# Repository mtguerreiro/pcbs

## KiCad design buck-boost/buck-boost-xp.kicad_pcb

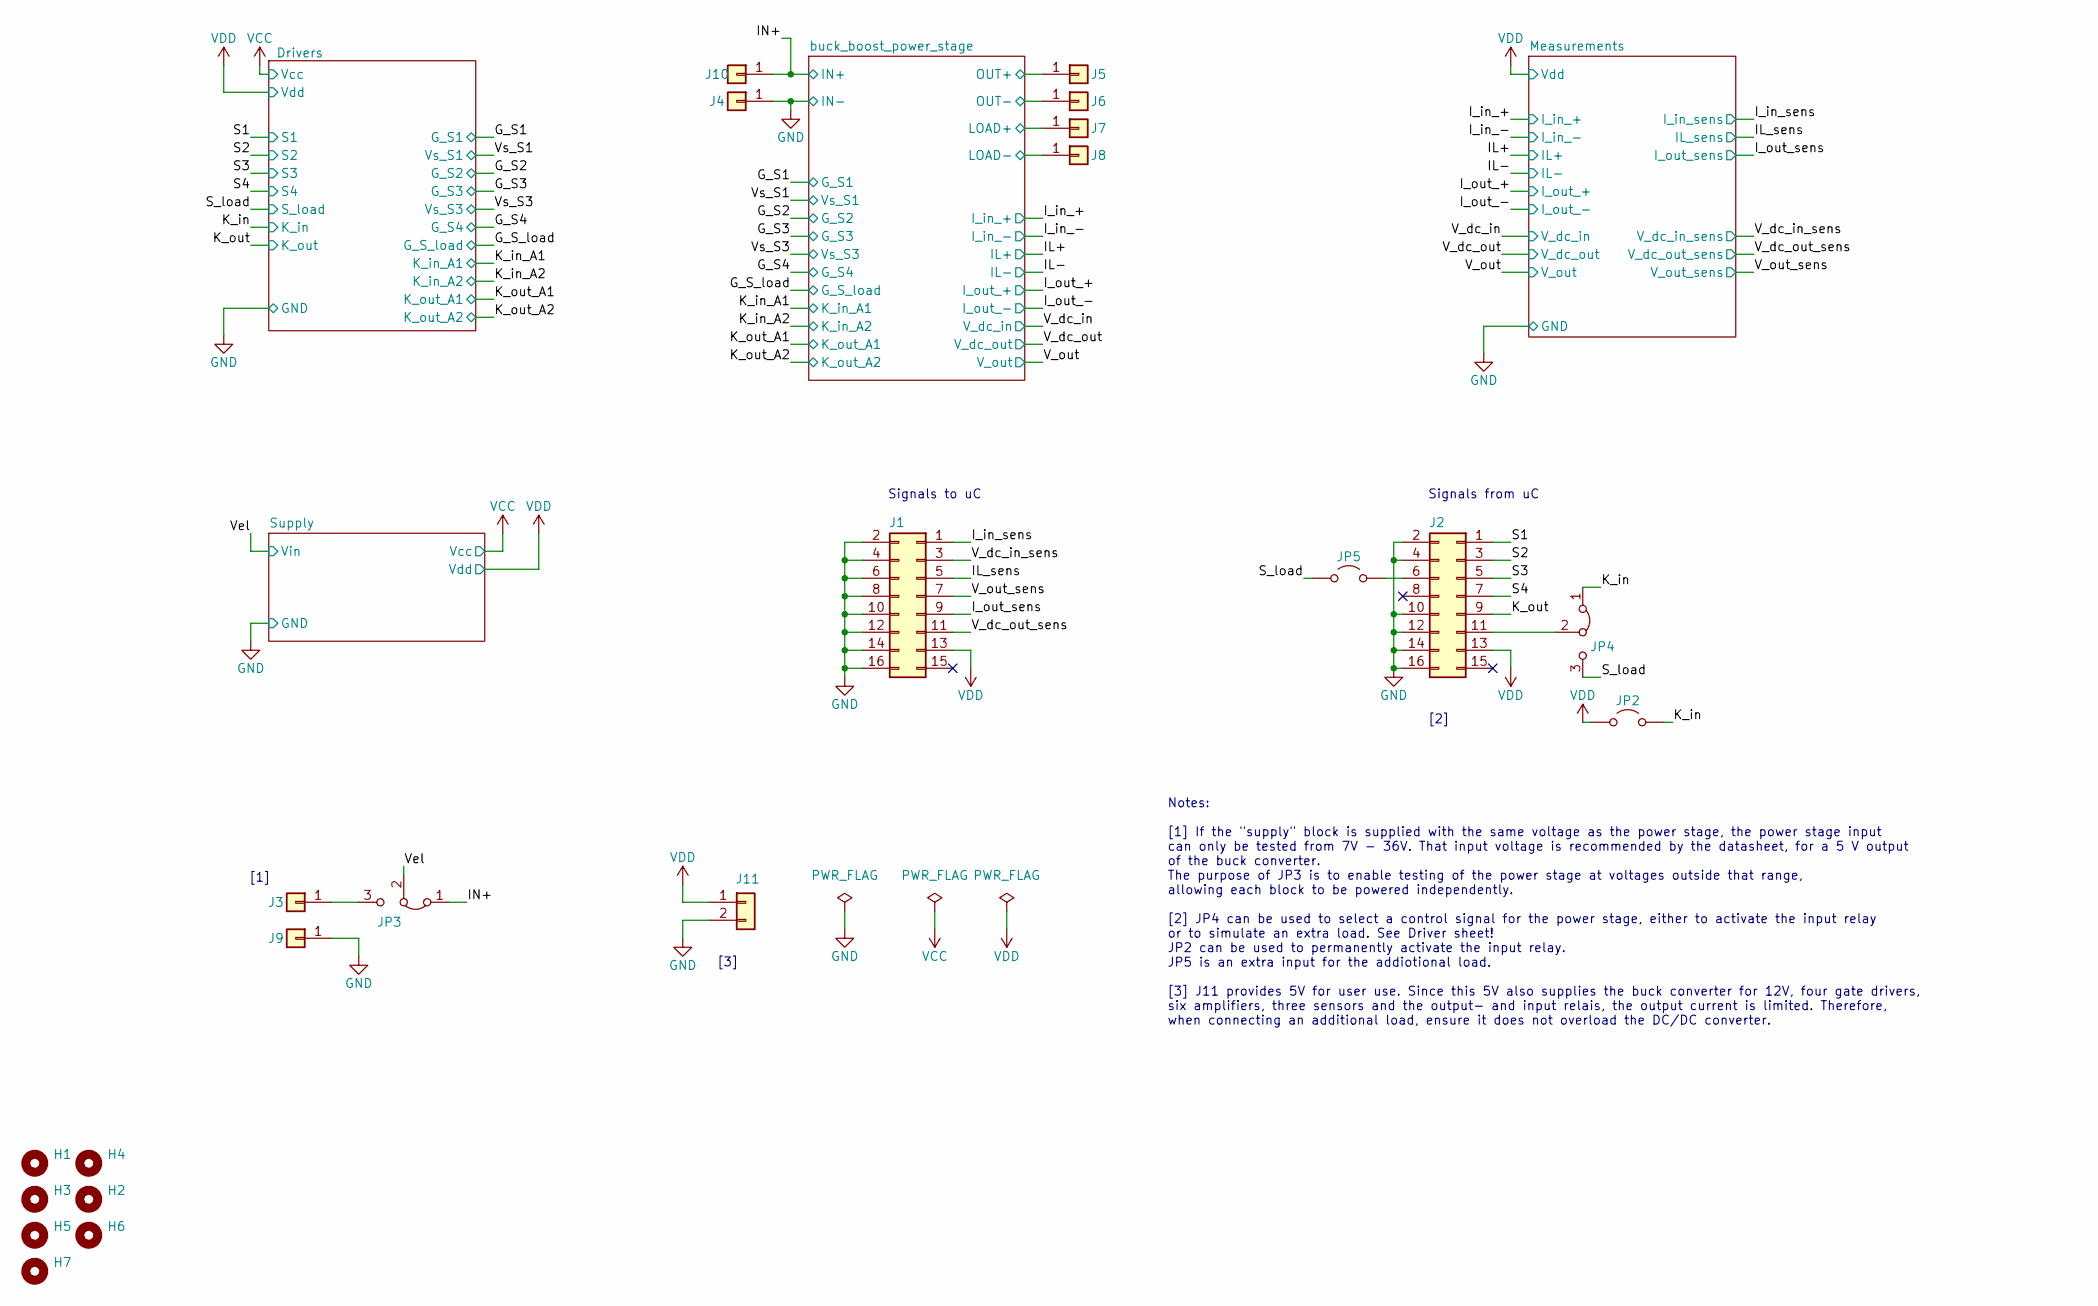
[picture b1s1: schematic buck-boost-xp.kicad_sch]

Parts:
H1, H2, H3, H4, H5, H6, H7: MountingHole; MountingHole_3.2mm_M3
J1, J2: Conn_02x08_Odd_Even; PinHeader_2x08_P2.54mm_Horizontal
J3, J4, J5, J6, J7, J8, J9, J10: Conn_01x01; MountingHole_6.4mm_M6_Pad
J11: Conn_01x02; PinHeader_1x02_P2.54mm_Vertical
JP2, JP5: Jumper_2_Open; TestPoint_2Pads_Pitch2.54mm_Drill0.8mm
JP3, JP4: Jumper_3_Bridged12; PinHeader_1x03_P2.54mm_Vertical

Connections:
/IL_sens: J1.5; also elsewhere on the board
/IN+: J10.1, JP3.1 (A); also elsewhere on the board
/I_in_sens: J1.1; also elsewhere on the board
/I_out_sens: J1.9; also elsewhere on the board
/K_in: JP2.2 (B), JP4.1 (A); also elsewhere on the board
/K_out: J2.9; also elsewhere on the board
/S1: J2.1; also elsewhere on the board
/S2: J2.3; also elsewhere on the board
/S3: J2.5; also elsewhere on the board
/S4: J2.7; also elsewhere on the board
/S_load: JP4.3 (B), JP5.1 (A); also elsewhere on the board
/V_dc_in_sens: J1.3; also elsewhere on the board
/V_dc_out_sens: J1.11; also elsewhere on the board
/V_out: J5.1, J7.1; also elsewhere on the board
/V_out_sens: J1.7; also elsewhere on the board
/Vel: JP3.2 (C); also elsewhere on the board
/buck_boost_power_stage/Load-: J8.1; also elsewhere on the board
GND: J1.2, J1.4, J1.6, J1.8, J1.10, J1.12, J1.14, J1.16, J2.2, J2.4, J2.10, J2.12, J2.14, J2.16, J4.1, J6.1, J9.1, J11.2; also elsewhere on the board
unnamed: J2.6, JP5.2 (B)
unnamed: J2.11, JP4.2 (C)
unnamed: J3.1, JP3.3 (B)
VDD: J1.13, J2.13, J11.1, JP2.1 (A); also elsewhere on the board

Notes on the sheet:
[1]
Signals from uC
Signals to uC
[3]
Notes: [1] If the "supply" block is supplied with the same voltage as the power stage, the power stage input can only be tested from 7V - 36V. That input voltage is recommended by the datasheet, for a 5 V output of the buck converter. The purpose of JP3 is to enable testing of the power stage at vo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
[2]

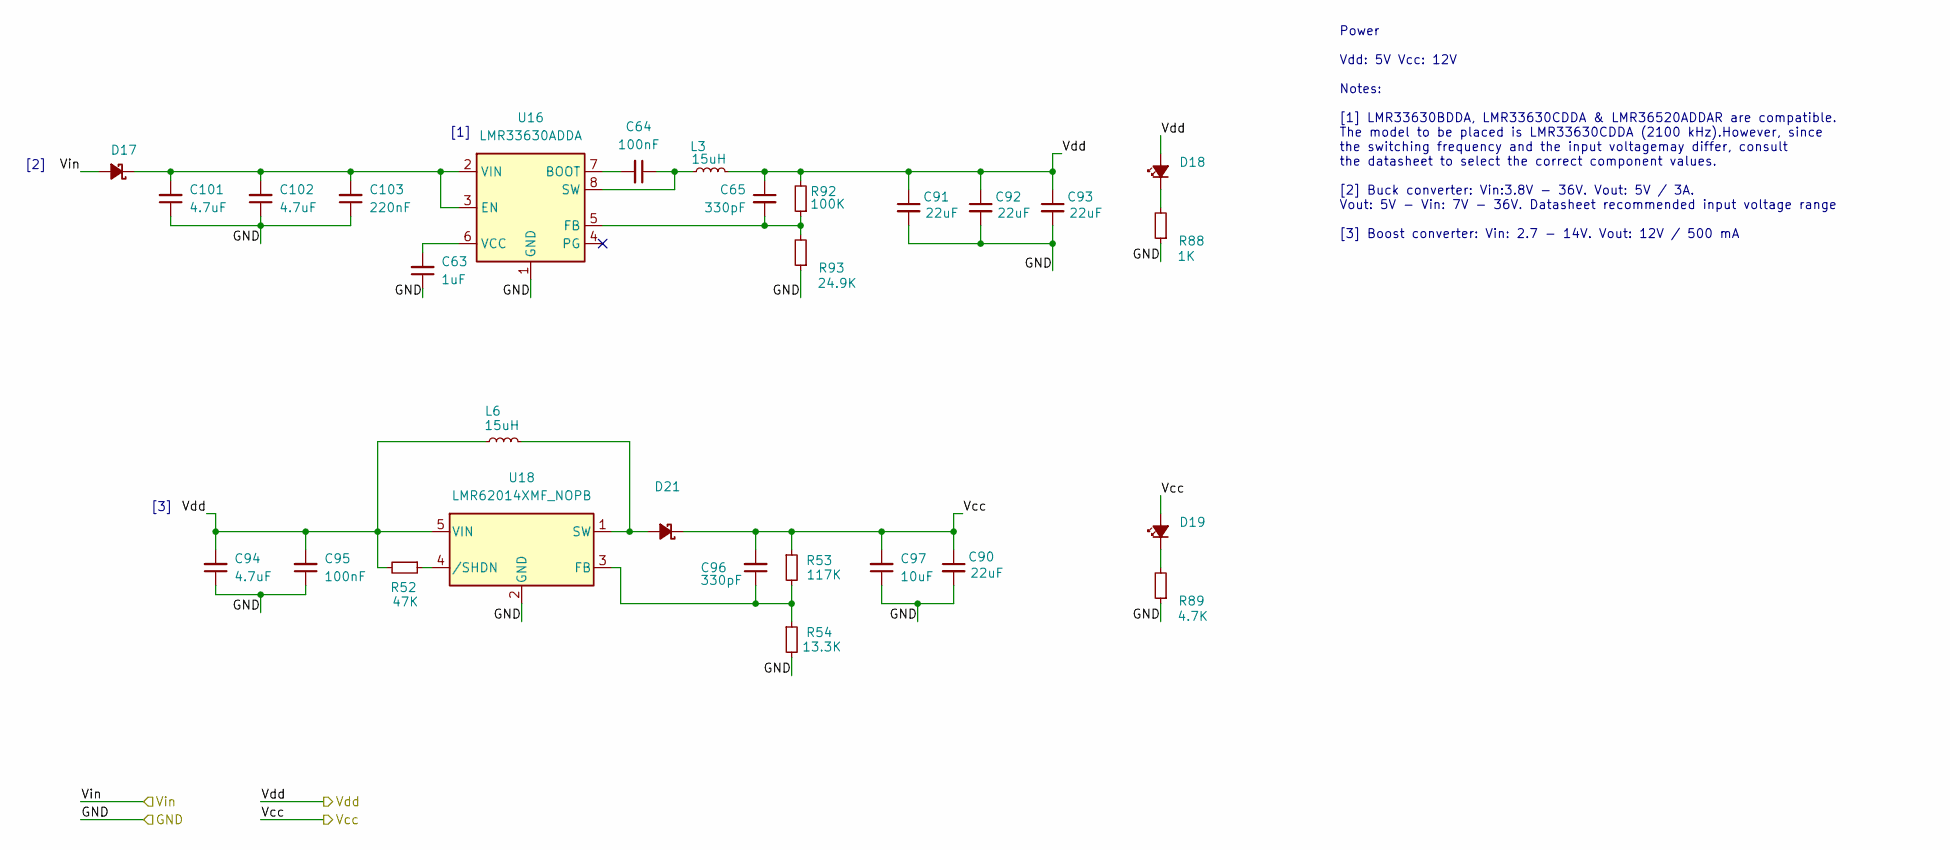
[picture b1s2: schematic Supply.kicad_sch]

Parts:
C63: 1uF; C_0805_2012Metric_Pad1.18x1.45mm_HandSolder
C64, C95: 100nF; C_0805_2012Metric_Pad1.18x1.45mm_HandSolder
C65, C96: 330pF; C_0805_2012Metric_Pad1.18x1.45mm_HandSolder
C90, C91, C92, C93: 22uF; C_1210_3225Metric_Pad1.33x2.70mm_HandSolder
C94, C101, C102: 4.7uF; C_0805_2012Metric_Pad1.18x1.45mm_HandSolder
C97: 10uF; C_0805_2012Metric_Pad1.18x1.45mm_HandSolder
C103: 220nF; C_0805_2012Metric_Pad1.18x1.45mm_HandSolder
D17, D21: D_Schottky_Small_Filled; D_SMB_Handsoldering
D18, D19: LED_Small_Filled; LED_0805_2012Metric_Pad1.15x1.40mm_HandSolder
L3, L6: 15uH; SRR1260-150M
R52: 47K; R_0805_2012Metric_Pad1.20x1.40mm_HandSolder
R53: 117K; R_0805_2012Metric_Pad1.20x1.40mm_HandSolder
R54: 13.3K; R_0805_2012Metric_Pad1.20x1.40mm_HandSolder
R88: 1K; R_0805_2012Metric_Pad1.20x1.40mm_HandSolder
R89: 4.7K; R_0805_2012Metric_Pad1.20x1.40mm_HandSolder
R92: 100K; R_0805_2012Metric_Pad1.20x1.40mm_HandSolder
R93: 24.9K; R_0805_2012Metric_Pad1.20x1.40mm_HandSolder
U16: LMR33630ADDA; Texas_HSOP-8-1EP_3.9x4.9mm_P1.27mm_ThermalVias
U18: LMR62014XMF_NOPB; SOT-23-5_HandSoldering

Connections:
/Vel: D17.2 (A); also elsewhere on the board
GND: C63.1, C90.2, C91.2, C92.2, C93.2, C94.1, C95.1, C97.1, C101.1, C102.1, C103.1, R54.2, R88.1, R89.1, R93.1, U16.1 (GND), U16.9 (GND), U18.2 (GND); also elsewhere on the board
unnamed: C101.2, C102.2, C103.2, D17.1 (K), U16.2 (VIN), U16.3 (EN)
unnamed: D18.1 (K), R88.2
unnamed: D19.1 (K), R89.2
unnamed: D21.2 (A), L6.2, U18.1 (SW)
unnamed: C64.2, U16.7 (BOOT)
unnamed: C65.2, R92.1, R93.2, U16.5 (FB)
unnamed: C64.1, L3.1, U16.8 (SW)
unnamed: C63.2, U16.6 (VCC)
unnamed: C96.1, R53.2, R54.1, U18.3 (FB)
unnamed: R52.1, U18.4 (/SHDN)
VCC: C90.1, C96.2, C97.2, D19.2 (A), D21.1 (K), R53.1; also elsewhere on the board
VDD: C65.1, C91.1, C92.1, C93.1, C94.2, C95.2, D18.2 (A), L3.2, L6.1, R52.2, R92.2, U18.5 (VIN); also elsewhere on the board

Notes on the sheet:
[2]
[1]
[3]
Power Vdd: 5V Vcc: 12V Notes: [1] LMR33630BDDA, LMR33630CDDA & LMR36520ADDAR are compatible. The model to be placed is LMR33630CDDA (2100 kHz).However, since the switching frequency and the input voltagemay differ, consult the datasheet to select the correct component values. [2] Buck converter: Vi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

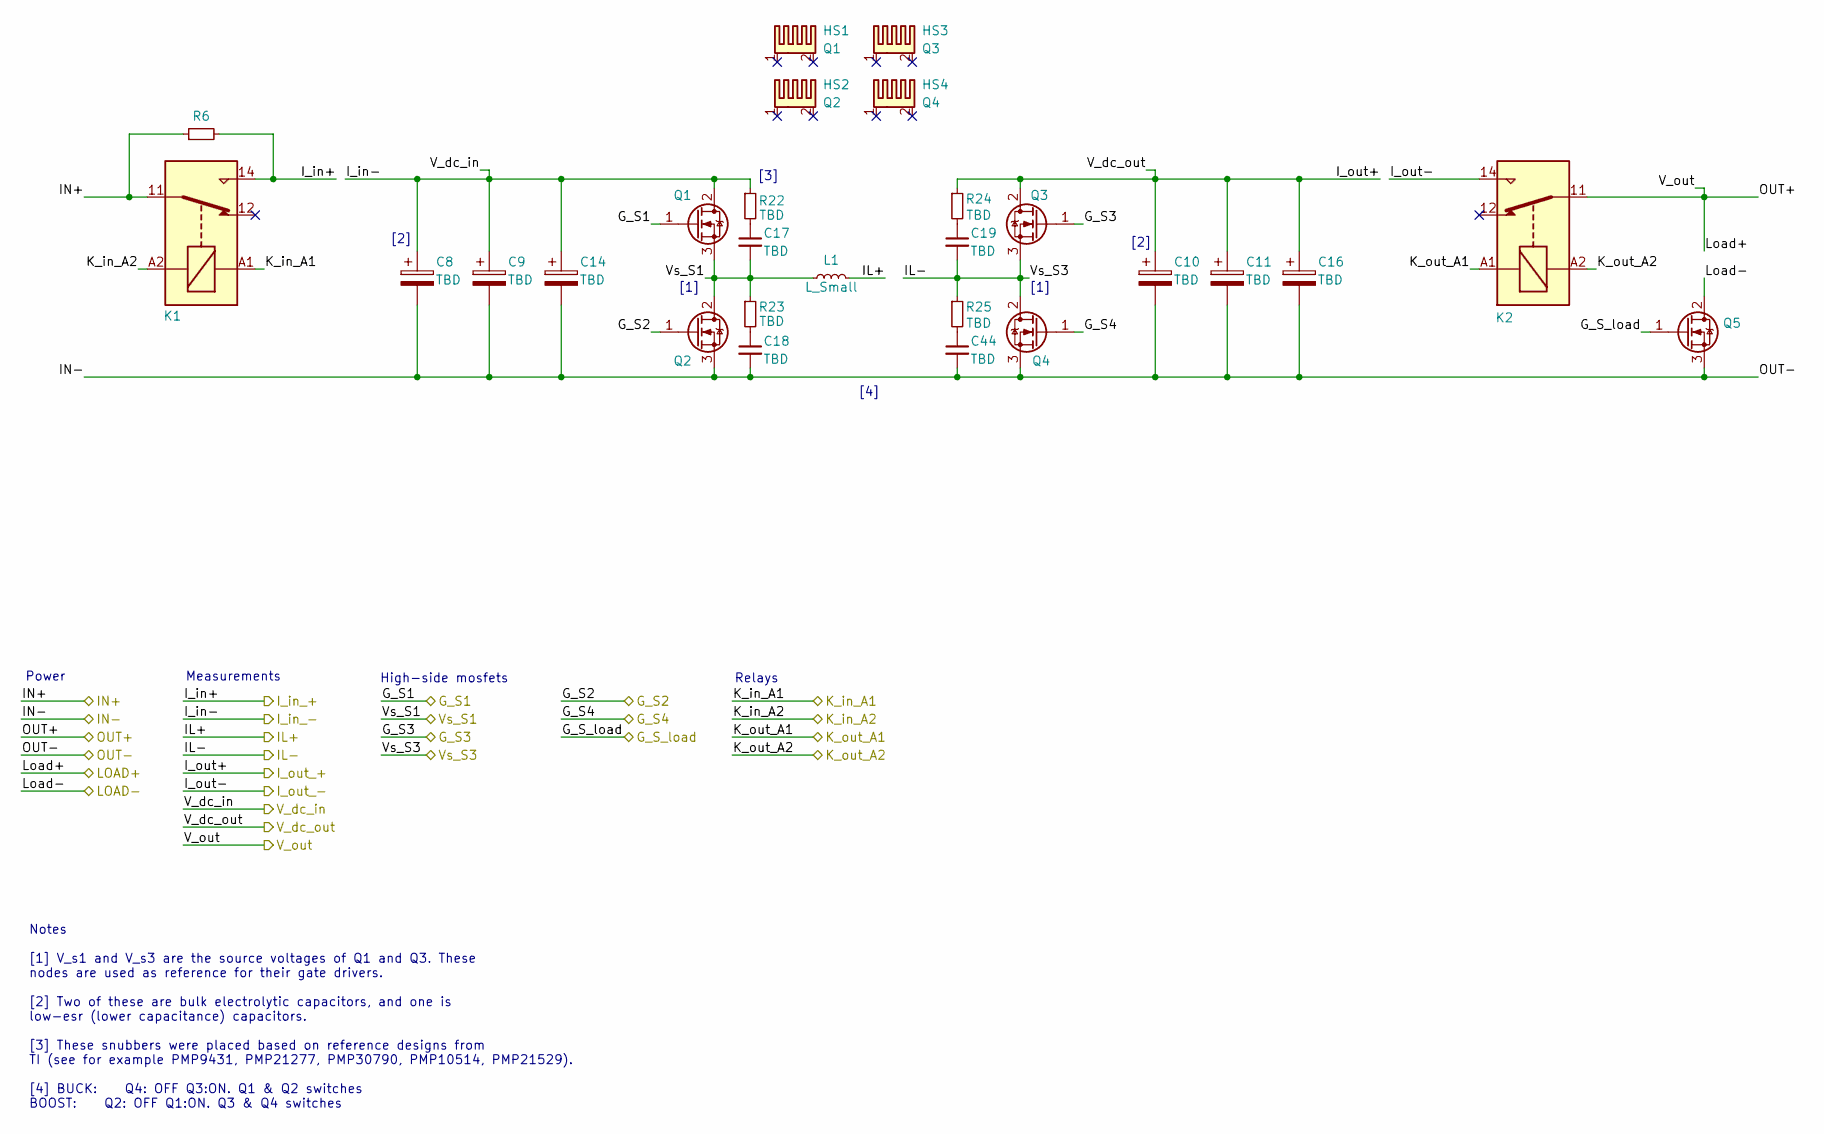
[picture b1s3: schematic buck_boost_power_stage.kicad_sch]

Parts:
C8, C9, C10, C11: TBD; CP_Radial_D18.0mm_P7.50mm
C14, C16: TBD; C_Rect_L43.0mm_W36.0mm_P37.50_27.50_22.50mm_S20.3_10.2mm_Fi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
C17, C18, C19, C44: TBD; C_1206_3216Metric_Pad1.33x1.80mm_HandSolder
HS1: Q1; Heatsink_Stonecold_HS-132_32x14mm_2xFixation1.5mm_2pins
HS2: Q2; Heatsink_Stonecold_HS-132_32x14mm_2xFixation1.5mm_2pins
HS3: Q3; Heatsink_Stonecold_HS-132_32x14mm_2xFixation1.5mm_2pins
HS4: Q4; Heatsink_Stonecold_HS-132_32x14mm_2xFixation1.5mm_2pins
K1, K2: Relay_SPDT; T9GV5L14-5
L1: L_Small; L_Bourns_SRP2313AA_24x24
Q1, Q2, Q3, Q4, Q5: Q_NMOS_GDS; TO-220-3_Vertical
R6: R_Small; R_MELF_MMB-0207_HandSoldering
R22, R23, R24, R25: TBD; R_MELF_MMB-0207_HandSoldering

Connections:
/G_S1: Q1.1 (G); also elsewhere on the board
/G_S2: Q2.1 (G); also elsewhere on the board
/G_S3: Q3.1 (G); also elsewhere on the board
/G_S4: Q4.1 (G); also elsewhere on the board
/G_S_load: Q5.1 (G); also elsewhere on the board
/IL+: L1.2; also elsewhere on the board
/IL-: C19.2, Q3.3 (S), Q4.2 (D), R25.1; also elsewhere on the board
/IN+: K1.11, R6.1; also elsewhere on the board
/I_in_+: K1.14, R6.2; also elsewhere on the board
/I_in_-: C8.1, C9.1, C14.1, Q1.2 (D), R22.1; also elsewhere on the board
/I_out_+: C10.1, C11.1, C16.1, Q3.2 (D), R24.1; also elsewhere on the board
/I_out_-: K2.14; also elsewhere on the board
/K_in_A2: K1.A2; also elsewhere on the board
/K_out_A2: K2.A2; also elsewhere on the board
/V_out: K2.11; also elsewhere on the board
/Vs_S1: C17.2, L1.1, Q1.3 (S), Q2.2 (D), R23.1; also elsewhere on the board
/buck_boost_power_stage/Load-: Q5.2 (D); also elsewhere on the board
GND: C8.2, C9.2, C10.2, C11.2, C14.2, C16.2, C18.2, C44.2, Q2.3 (S), Q4.3 (S), Q5.3 (S); also elsewhere on the board
unnamed: C17.1, R22.2
unnamed: C18.1, R23.2
unnamed: C19.1, R24.2
unnamed: C44.1, R25.2
VDD: K1.A1, K2.A1; also elsewhere on the board

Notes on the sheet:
[1]
Notes [1] V_s1 and V_s3 are the source voltages of Q1 and Q3. These nodes are used as reference for their gate drivers. [2] Two of these are bulk electrolytic capacitors, and one is low-esr (lower capacitance) capacitors. [3] These snubbers were placed based on reference designs from TI (see for ex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
[2]
Relays
[3]
Power
[4]
High-side mosfets
Measurements

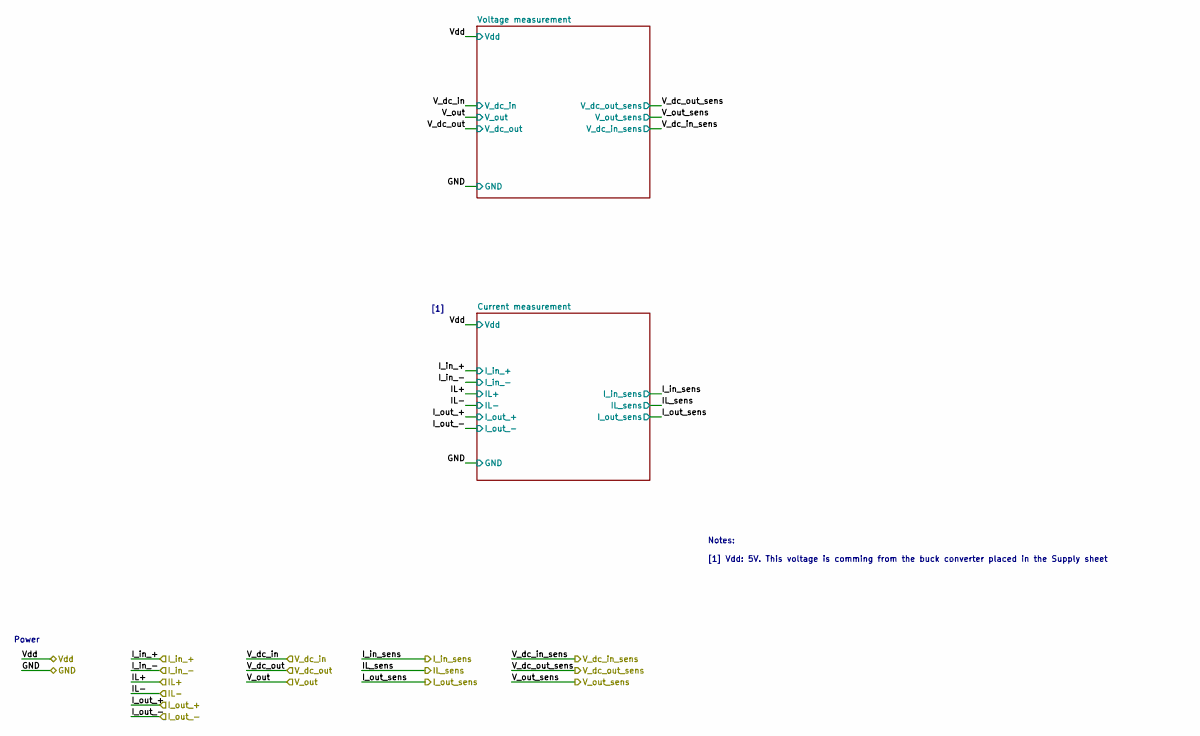
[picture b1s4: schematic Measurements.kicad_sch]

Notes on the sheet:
Notes: [1] Vdd: 5V. This voltage is comming from the buck converter placed in the Supply sheet
Power
[1]

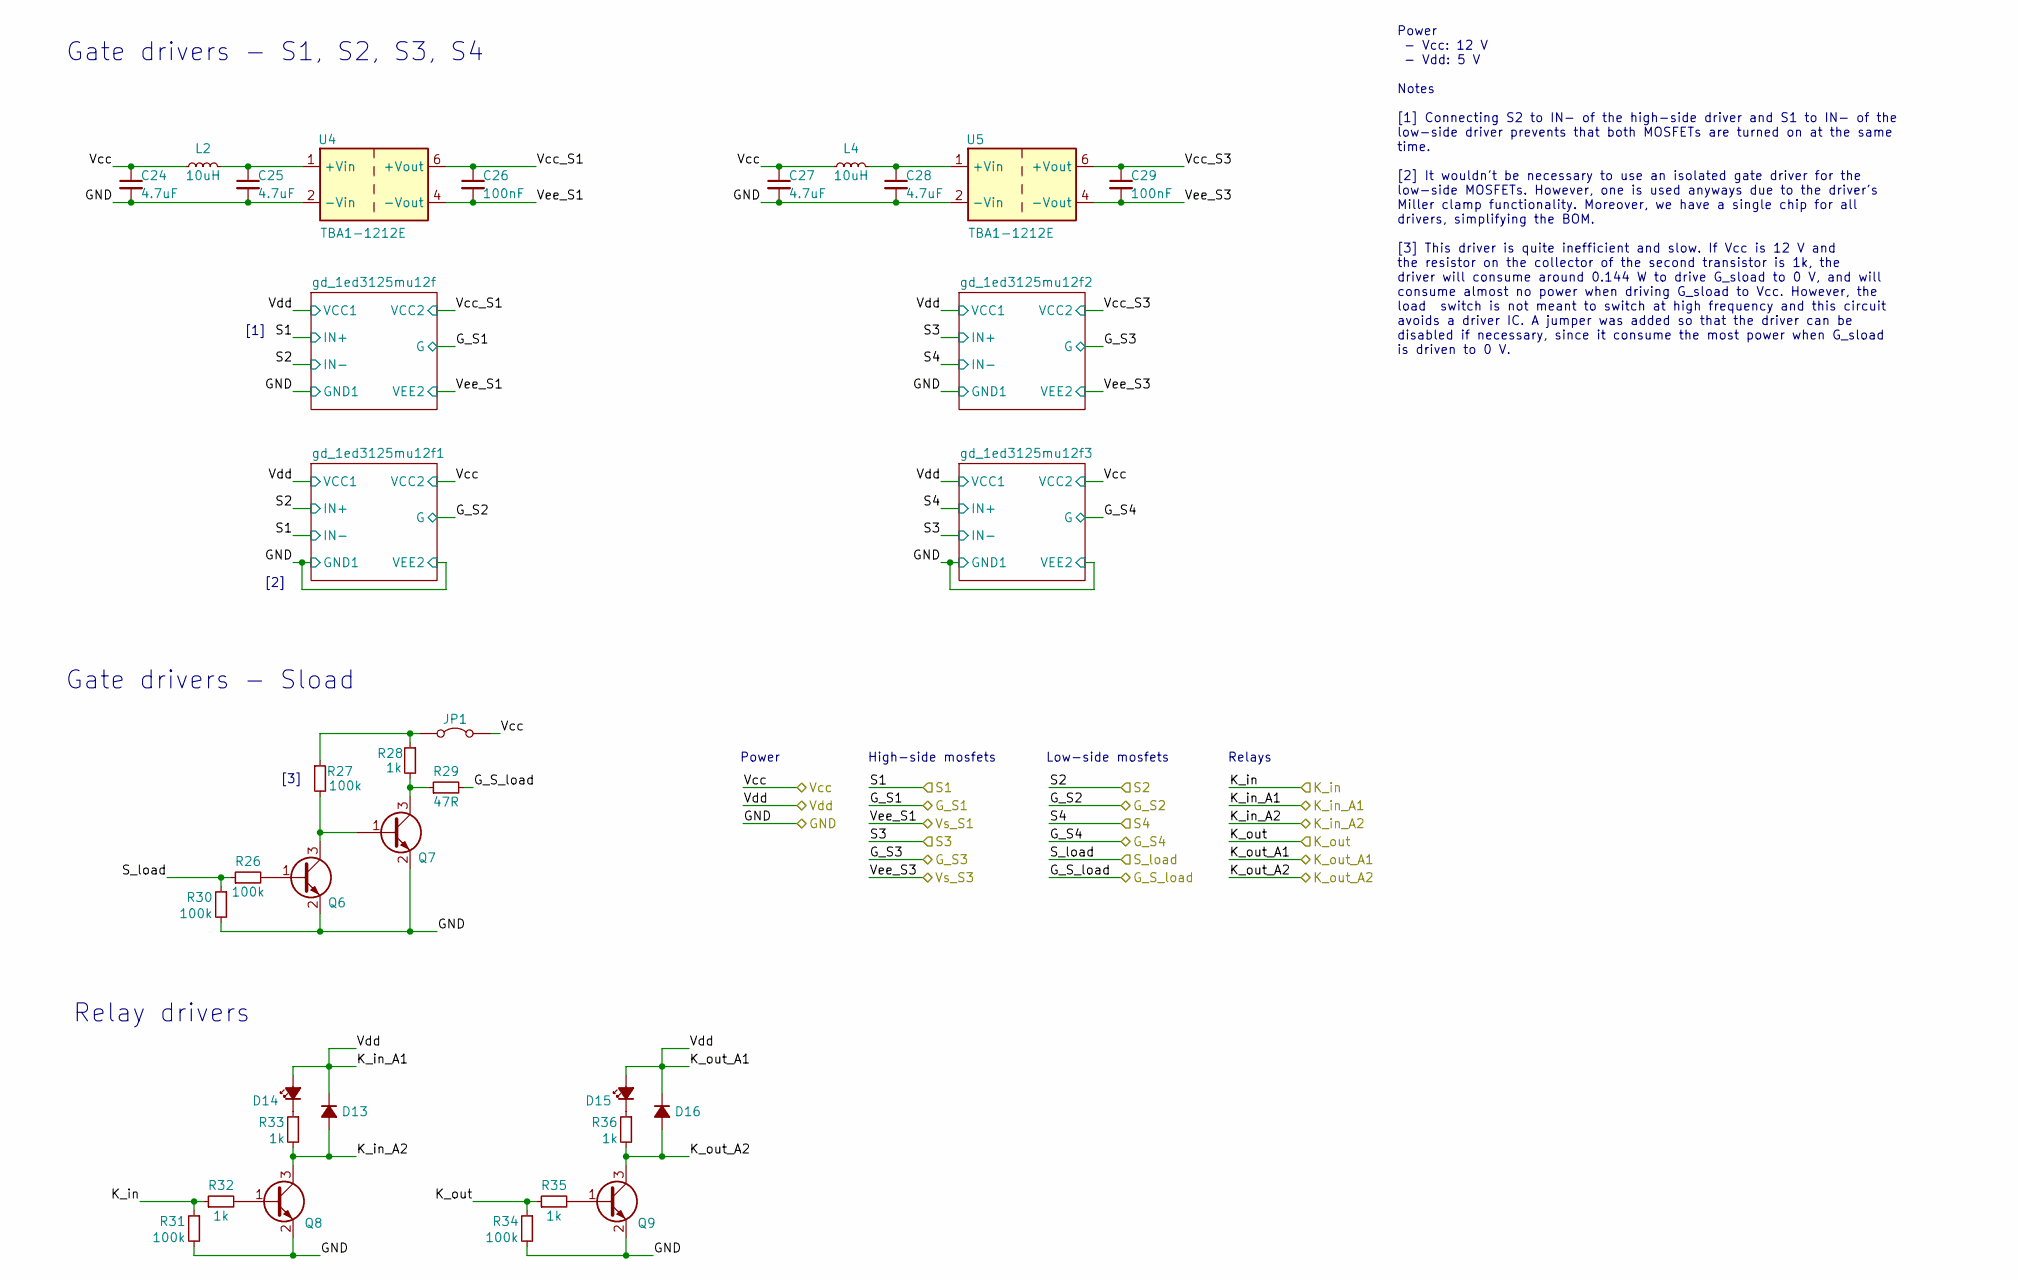
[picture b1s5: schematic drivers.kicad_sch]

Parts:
C24, C25, C27, C28: 4.7uF; C_0805_2012Metric_Pad1.18x1.45mm_HandSolder
C26, C29: 100nF; C_0805_2012Metric_Pad1.18x1.45mm_HandSolder
D13, D16: D_Small_Filled; D_SOD-123
D14, D15: LED_Small_Filled; LED_0805_2012Metric_Pad1.15x1.40mm_HandSolder
JP1: Jumper_2_Bridged; TestPoint_2Pads_Pitch2.54mm_Drill0.8mm
L2, L4: 10uH; L_0805_2012Metric_Pad1.15x1.40mm_HandSolder
Q6, Q7, Q8, Q9: Q_NPN_BEC; SOT-23W_Handsoldering
R26, R27, R30, R31, R34: 100k; R_0805_2012Metric_Pad1.20x1.40mm_HandSolder
R28, R32, R33, R35, R36: 1k; R_0805_2012Metric_Pad1.20x1.40mm_HandSolder
R29: 47R; R_0805_2012Metric_Pad1.20x1.40mm_HandSolder
U4, U5: TBA1-1212E; Converter_DCDC_TRACO_TBA1-xxxxE_Single_THT

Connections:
/Drivers/Vcc_S1: C26.1, U4.6 (+Vout); also elsewhere on the board
/Drivers/Vcc_S3: C29.1, U5.6 (+Vout); also elsewhere on the board
/G_S_load: R29.2; also elsewhere on the board
/IL-: C29.2, U5.4 (-Vout); also elsewhere on the board
/K_in: R31.1, R32.1; also elsewhere on the board
/K_in_A2: D13.2 (A), Q8.3 (C), R33.2; also elsewhere on the board
/K_out: R34.1, R35.1; also elsewhere on the board
/K_out_A2: D16.2 (A), Q9.3 (C), R36.2; also elsewhere on the board
/S_load: R26.1, R30.1; also elsewhere on the board
/Vs_S1: C26.2, U4.4 (-Vout); also elsewhere on the board
GND: C24.2, C25.2, C27.2, C28.2, Q6.2 (E), Q7.2 (E), Q8.2 (E), Q9.2 (E), R30.2, R31.2, R34.2, U4.2 (-Vin), U5.2 (-Vin); also elsewhere on the board
unnamed: D14.1 (K), R33.1
unnamed: D15.1 (K), R36.1
unnamed: JP1.1 (A), R27.1, R28.1
unnamed: Q6.1 (B), R26.2
unnamed: Q6.3 (C), Q7.1 (B), R27.2
unnamed: Q7.3 (C), R28.2, R29.1
unnamed: Q8.1 (B), R32.2
unnamed: Q9.1 (B), R35.2
unnamed: C25.1, L2.2, U4.1 (+Vin)
unnamed: C28.1, L4.2, U5.1 (+Vin)
VCC: C24.1, C27.1, JP1.2 (B), L2.1, L4.1; also elsewhere on the board
VDD: D13.1 (K), D14.2 (A), D15.2 (A), D16.1 (K); also elsewhere on the board

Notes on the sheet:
Relay drivers
Power
Power - Vcc: 12 V - Vdd: 5 V Notes [1] Connecting S2 to IN- of the high-side driver and S1 to IN- of the low-side driver prevents that both MOSFETs are turned on at the same time. [2] It wouldn't be necessary to use an isolated gate driver for the low-side MOSFETs. However, one is used anyways due 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
Relays
High-side mosfets
Gate drivers - Sload
[3]
Gate drivers - S1, S2, S3, S4
Low-side mosfets
[1]
[2]

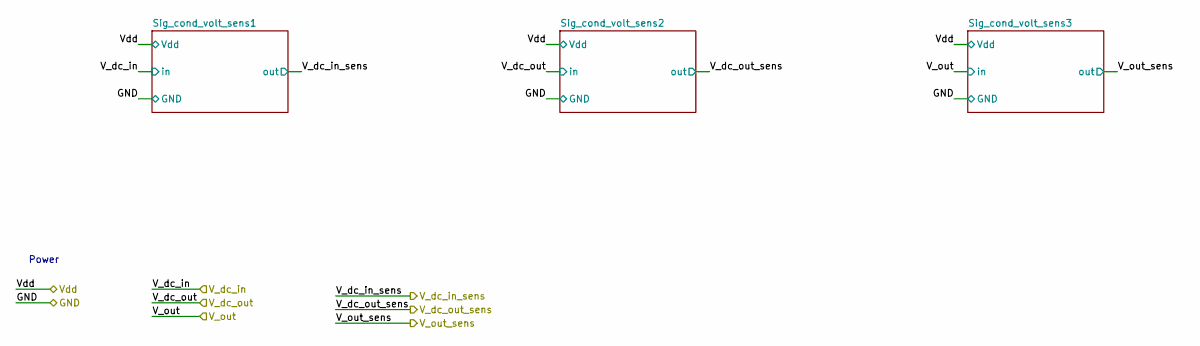
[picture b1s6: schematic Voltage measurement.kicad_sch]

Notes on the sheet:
Power

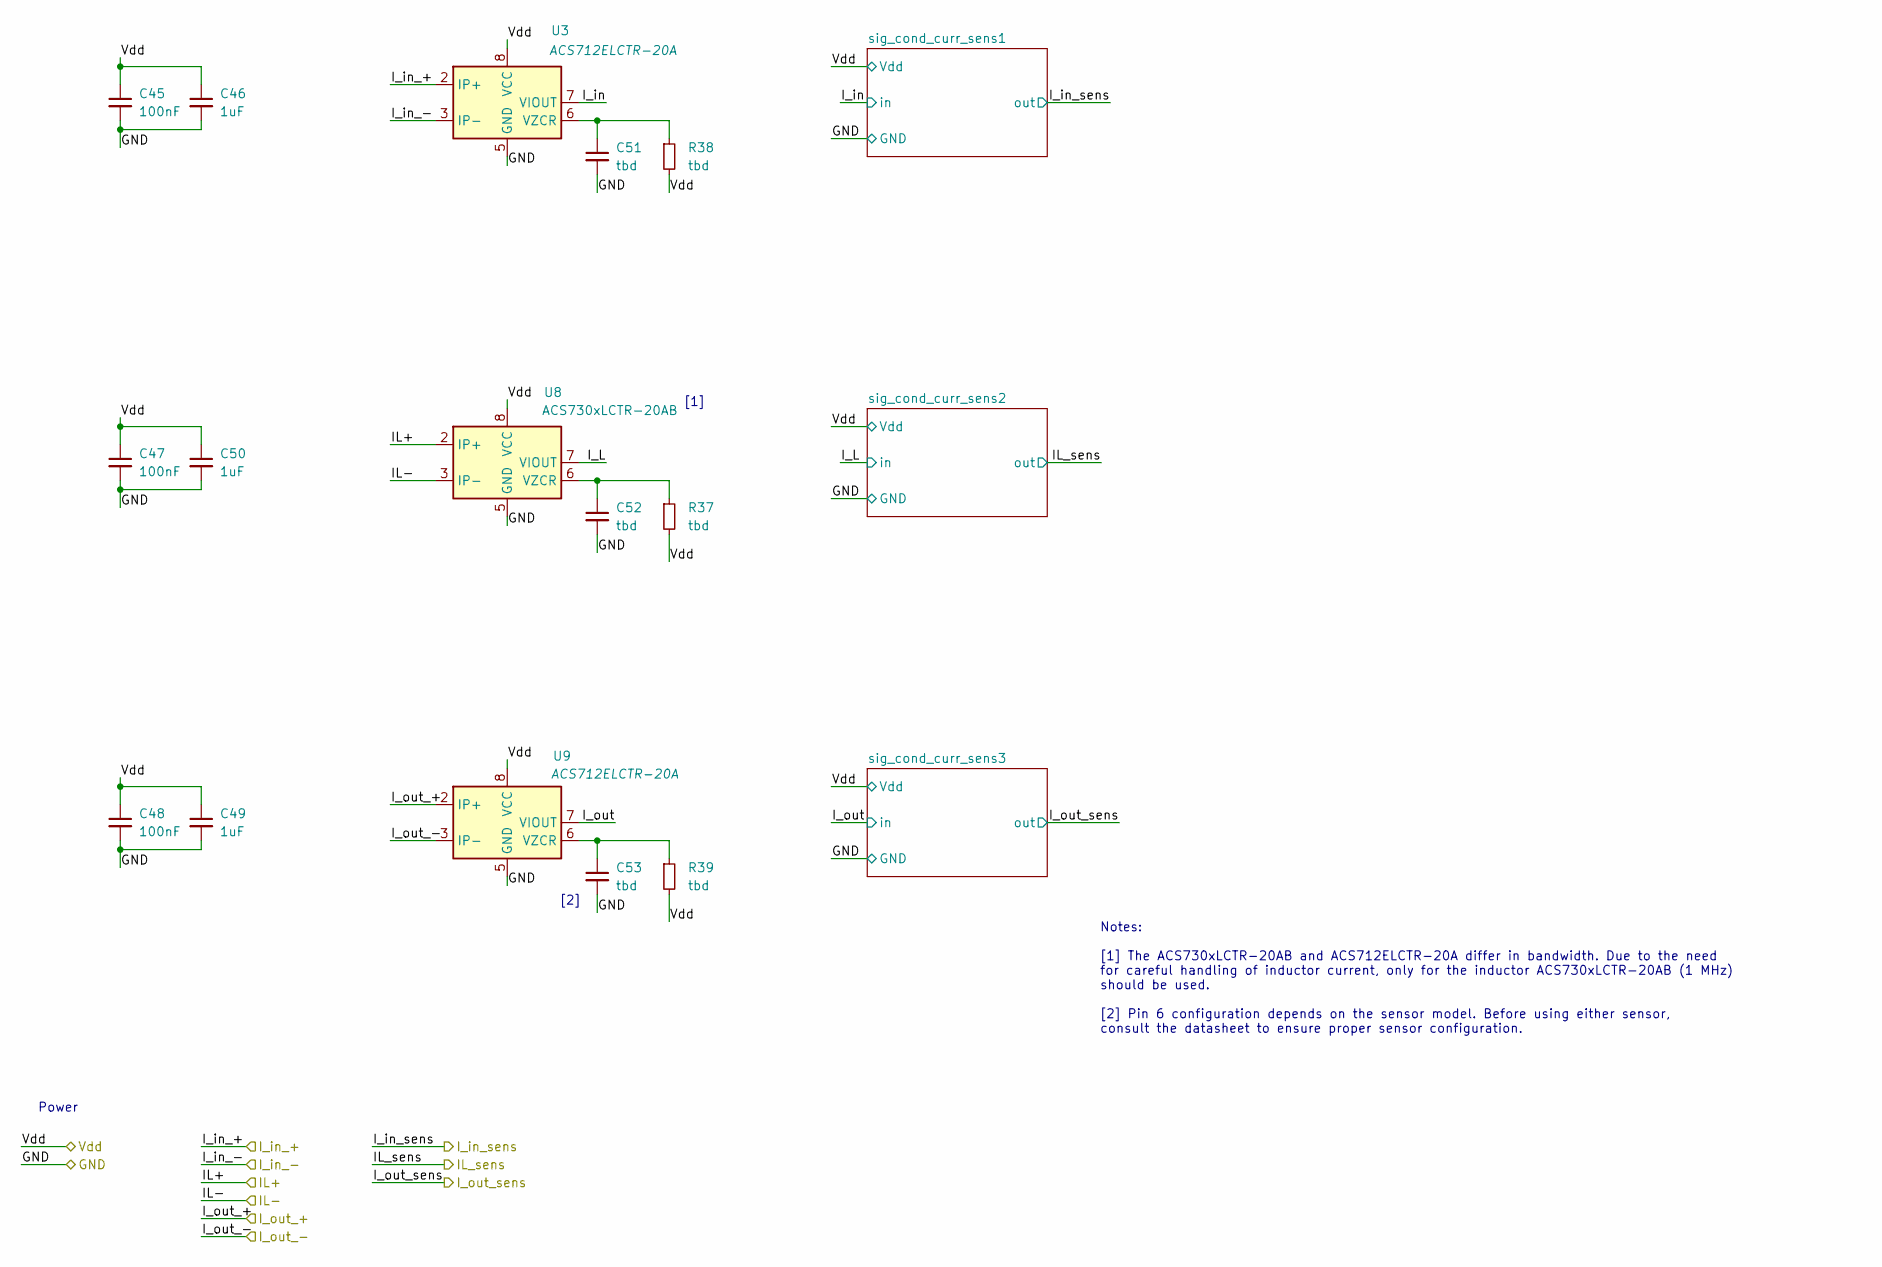
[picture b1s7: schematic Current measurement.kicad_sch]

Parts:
C45, C47, C48: 100nF; C_0805_2012Metric_Pad1.18x1.45mm_HandSolder
C46, C49, C50: 1uF; C_0805_2012Metric_Pad1.18x1.45mm_HandSolder
C51, C52, C53: tbd; C_0805_2012Metric_Pad1.18x1.45mm_HandSolder
R37, R38, R39: tbd; R_0805_2012Metric_Pad1.20x1.40mm_HandSolder
U3, U9: ACS712ELCTR-20A; SOIC-8_3.9x4.9mm_P1.27mm
U8: ACS730xLCTR-20AB; SOIC-8_3.9x4.9mm_P1.27mm

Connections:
/IL+: U8.1 (IP+), U8.2 (IP+); also elsewhere on the board
/IL-: U8.3 (IP-), U8.4 (IP-); also elsewhere on the board
/I_in_+: U3.1 (IP+), U3.2 (IP+); also elsewhere on the board
/I_in_-: U3.3 (IP-), U3.4 (IP-); also elsewhere on the board
/I_out_+: U9.1 (IP+), U9.2 (IP+); also elsewhere on the board
/I_out_-: U9.3 (IP-), U9.4 (IP-); also elsewhere on the board
/Measurements/Current measurement/I_L: U8.7 (VIOUT); also elsewhere on the board
/Measurements/Current measurement/I_in: U3.7 (VIOUT); also elsewhere on the board
/Measurements/Current measurement/I_out: U9.7 (VIOUT); also elsewhere on the board
GND: C45.2, C46.2, C47.2, C48.2, C49.2, C50.2, C51.2, C52.2, C53.2, U3.5 (GND), U8.5 (GND), U9.5 (GND); also elsewhere on the board
unnamed: C51.1, R38.1, U3.6 (VZCR)
unnamed: C52.1, R37.1, U8.6 (VZCR)
unnamed: C53.1, R39.1, U9.6 (VZCR)
VDD: C45.1, C46.1, C47.1, C48.1, C49.1, C50.1, R37.2, R38.2, R39.2, U3.8 (VCC), U8.8 (VCC), U9.8 (VCC); also elsewhere on the board

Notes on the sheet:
Power
[2]
Notes: [1] The ACS730xLCTR-20AB and ACS712ELCTR-20A differ in bandwidth. Due to the need for careful handling of inductor current, only for the inductor ACS730xLCTR-20AB (1 MHz) should be used. [2] Pin 6 configuration depends on the sensor model. Before using either sensor, consult the datasheet to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
[1]

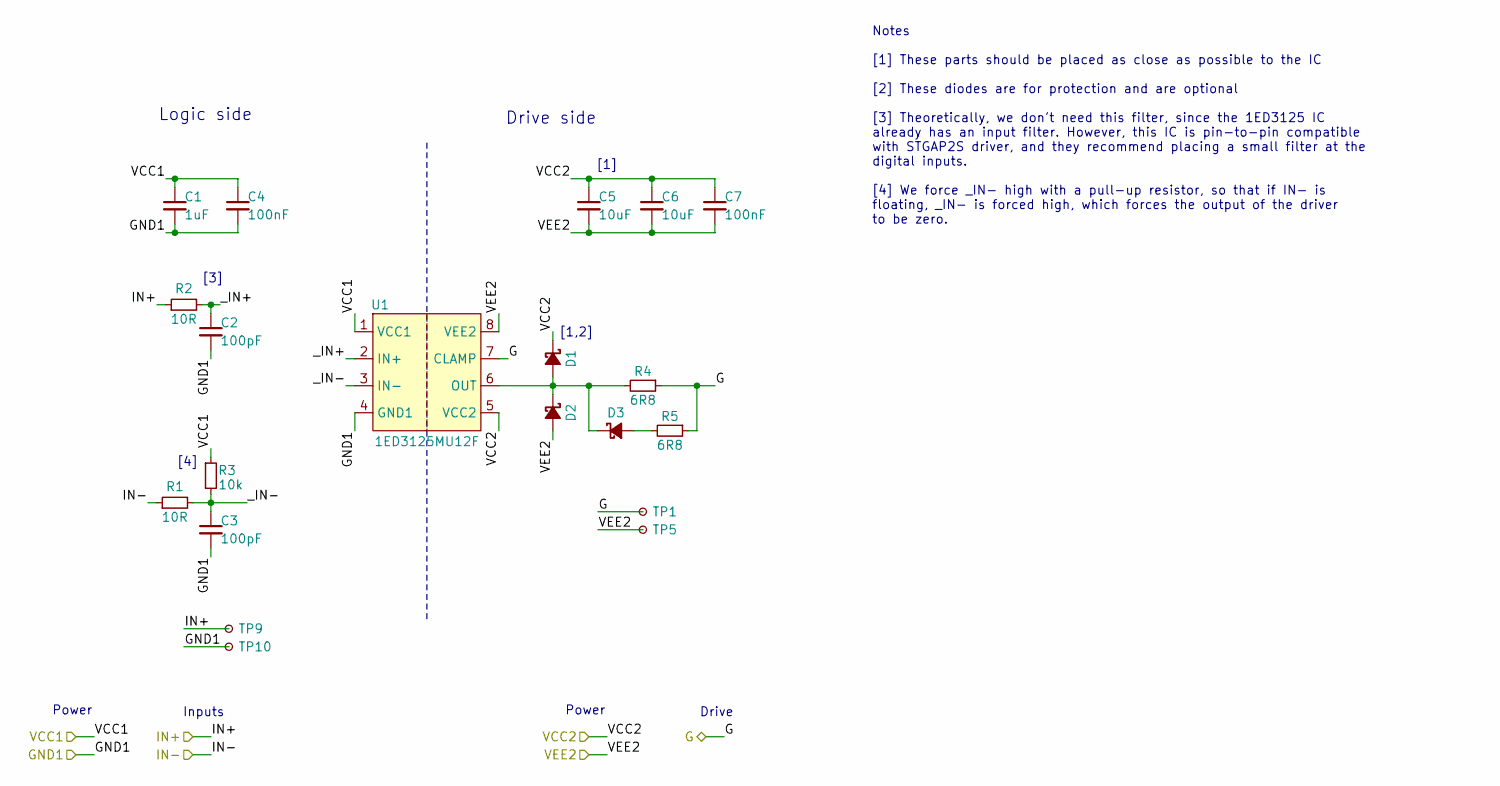
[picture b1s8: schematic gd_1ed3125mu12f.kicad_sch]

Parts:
C1: 1uF; C_0805_2012Metric_Pad1.18x1.45mm_HandSolder
C2, C3: 100pF; C_0805_2012Metric_Pad1.18x1.45mm_HandSolder
C4, C7: 100nF; C_0805_2012Metric_Pad1.18x1.45mm_HandSolder
C5, C6: 10uF; C_0805_2012Metric_Pad1.18x1.45mm_HandSolder
D1, D2, D3: D_Schottky_Small_Filled; D_SOD-123
R1, R2: 10R; R_0805_2012Metric_Pad1.20x1.40mm_HandSolder
R3: 10k; R_0805_2012Metric_Pad1.20x1.40mm_HandSolder
R4, R5: 6R8; R_MELF_MMB-0207
TP1, TP5, TP9, TP10: TestPoint_Small; PinHeader_1x01_P2.54mm_Vertical
U1: 1ED3125MU12F; SO-8_3.9x4.9mm_P1.27mm

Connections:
/Drivers/Vcc_S1: C5.1, C6.1, C7.1, D1.1 (K), U1.5 (VCC2); also elsewhere on the board
/Drivers/gd_1ed3125mu12f/_IN+: C2.1, R2.2, U1.2 (IN+)
/Drivers/gd_1ed3125mu12f/_IN-: C3.1, R1.2, R3.2, U1.3 (IN-)
/G_S1: R4.1, R5.1, TP1.1, U1.7 (CLAMP); also elsewhere on the board
/S1: R2.1, TP9.1; also elsewhere on the board
/S2: R1.1; also elsewhere on the board
/Vs_S1: C5.2, C6.2, C7.2, D2.2 (A), TP5.1, U1.8 (VEE2); also elsewhere on the board
GND: C1.2, C2.2, C3.2, C4.2, TP10.1, U1.4 (GND1); also elsewhere on the board
unnamed: D1.2 (A), D2.1 (K), D3.1 (K), R4.2, U1.6 (OUT)
unnamed: D3.2 (A), R5.2
VDD: C1.1, C4.1, R3.1, U1.1 (VCC1); also elsewhere on the board

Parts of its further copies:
C12, C30, C37: 1uF; C_0805_2012Metric_Pad1.18x1.45mm_HandSolder
C13, C15, C31, C32, C38, C39: 100pF; C_0805_2012Metric_Pad1.18x1.45mm_HandSolder
C20, C23, C33, C36, C40, C43: 100nF; C_0805_2012Metric_Pad1.18x1.45mm_HandSolder
C21, C22, C34, C35, C41, C42: 10uF; C_0805_2012Metric_Pad1.18x1.45mm_HandSolder
D4, D5, D6, D7, D8, D9, D10, D11, D12: D_Schottky_Small_Filled; D_SOD-123
R7, R8, R12, R13, R17, R18: 10R; R_0805_2012Metric_Pad1.20x1.40mm_HandSolder
R9, R14, R19: 10k; R_0805_2012Metric_Pad1.20x1.40mm_HandSolder
R10, R11, R15, R16, R20, R21: 6R8; R_MELF_MMB-0207
TP2, TP3, TP4, TP6, TP7, TP8, TP11, TP12, TP13, TP14, TP15, TP16: TestPoint_Small; PinHeader_1x01_P2.54mm_Vertical
U2, U6, U7: 1ED3125MU12F; SO-8_3.9x4.9mm_P1.27mm

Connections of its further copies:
/Drivers/Vcc_S3: C34.1, C35.1, C36.1, D7.1 (K), U6.5 (VCC2); also elsewhere on the board
/Drivers/gd_1ed3125mu12f1/_IN+: C13.1, R8.2, U2.2 (IN+)
/Drivers/gd_1ed3125mu12f1/_IN-: C15.1, R7.2, R9.2, U2.3 (IN-)
/Drivers/gd_1ed3125mu12f2/_IN+: C31.1, R13.2, U6.2 (IN+)
/Drivers/gd_1ed3125mu12f2/_IN-: C32.1, R12.2, R14.2, U6.3 (IN-)
/Drivers/gd_1ed3125mu12f3/_IN+: C38.1, R18.2, U7.2 (IN+)
/Drivers/gd_1ed3125mu12f3/_IN-: C39.1, R17.2, R19.2, U7.3 (IN-)
/G_S2: R10.1, R11.1, TP2.1, U2.7 (CLAMP); also elsewhere on the board
/G_S3: R15.1, R16.1, TP3.1, U6.7 (CLAMP); also elsewhere on the board
/G_S4: R20.1, R21.1, TP4.1, U7.7 (CLAMP); also elsewhere on the board
/IL-: C34.2, C35.2, C36.2, D8.2 (A), TP7.1, U6.8 (VEE2); also elsewhere on the board
/S1: R7.1; also elsewhere on the board
/S2: R8.1, TP11.1; also elsewhere on the board
/S3: R13.1, R17.1, TP13.1; also elsewhere on the board
/S4: R12.1, R18.1, TP15.1; also elsewhere on the board
GND: C12.2, C13.2, C15.2, C20.2, C21.2, C22.2, C23.2, C30.2, C31.2, C32.2, C33.2, C37.2, C38.2, C39.2, C40.2, C41.2, C42.2, C43.2, D5.2 (A), D11.2 (A), TP6.1, TP8.1, TP12.1, TP14.1, TP16.1, U2.4 (GND1), U2.8 (VEE2), U6.4 (GND1), U7.4 (GND1), U7.8 (VEE2); also elsewhere on the board
unnamed: D4.2 (A), D5.1 (K), D6.1 (K), R10.2, U2.6 (OUT)
unnamed: D6.2 (A), R11.2
unnamed: D7.2 (A), D8.1 (K), D9.1 (K), R15.2, U6.6 (OUT)
unnamed: D9.2 (A), R16.2
unnamed: D10.2 (A), D11.1 (K), D12.1 (K), R20.2, U7.6 (OUT)
unnamed: D12.2 (A), R21.2
VCC: C21.1, C22.1, C23.1, C41.1, C42.1, C43.1, D4.1 (K), D10.1 (K), U2.5 (VCC2), U7.5 (VCC2); also elsewhere on the board
VDD: C12.1, C20.1, C30.1, C33.1, C37.1, C40.1, R9.1, R14.1, R19.1, U2.1 (VCC1), U6.1 (VCC1), U7.1 (VCC1); also elsewhere on the board

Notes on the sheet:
Drive side
Inputs
Drive
Power
[4]
Notes [1] These parts should be placed as close as possible to the IC [2] These diodes are for protection and are optional [3] Theoretically, we don't need this filter, since the 1ED3125 IC already has an input filter. However, this IC is pin-to-pin compatible with STGAP2S driver, and they recommen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
[3]
[1]
Logic side
[1,2]
